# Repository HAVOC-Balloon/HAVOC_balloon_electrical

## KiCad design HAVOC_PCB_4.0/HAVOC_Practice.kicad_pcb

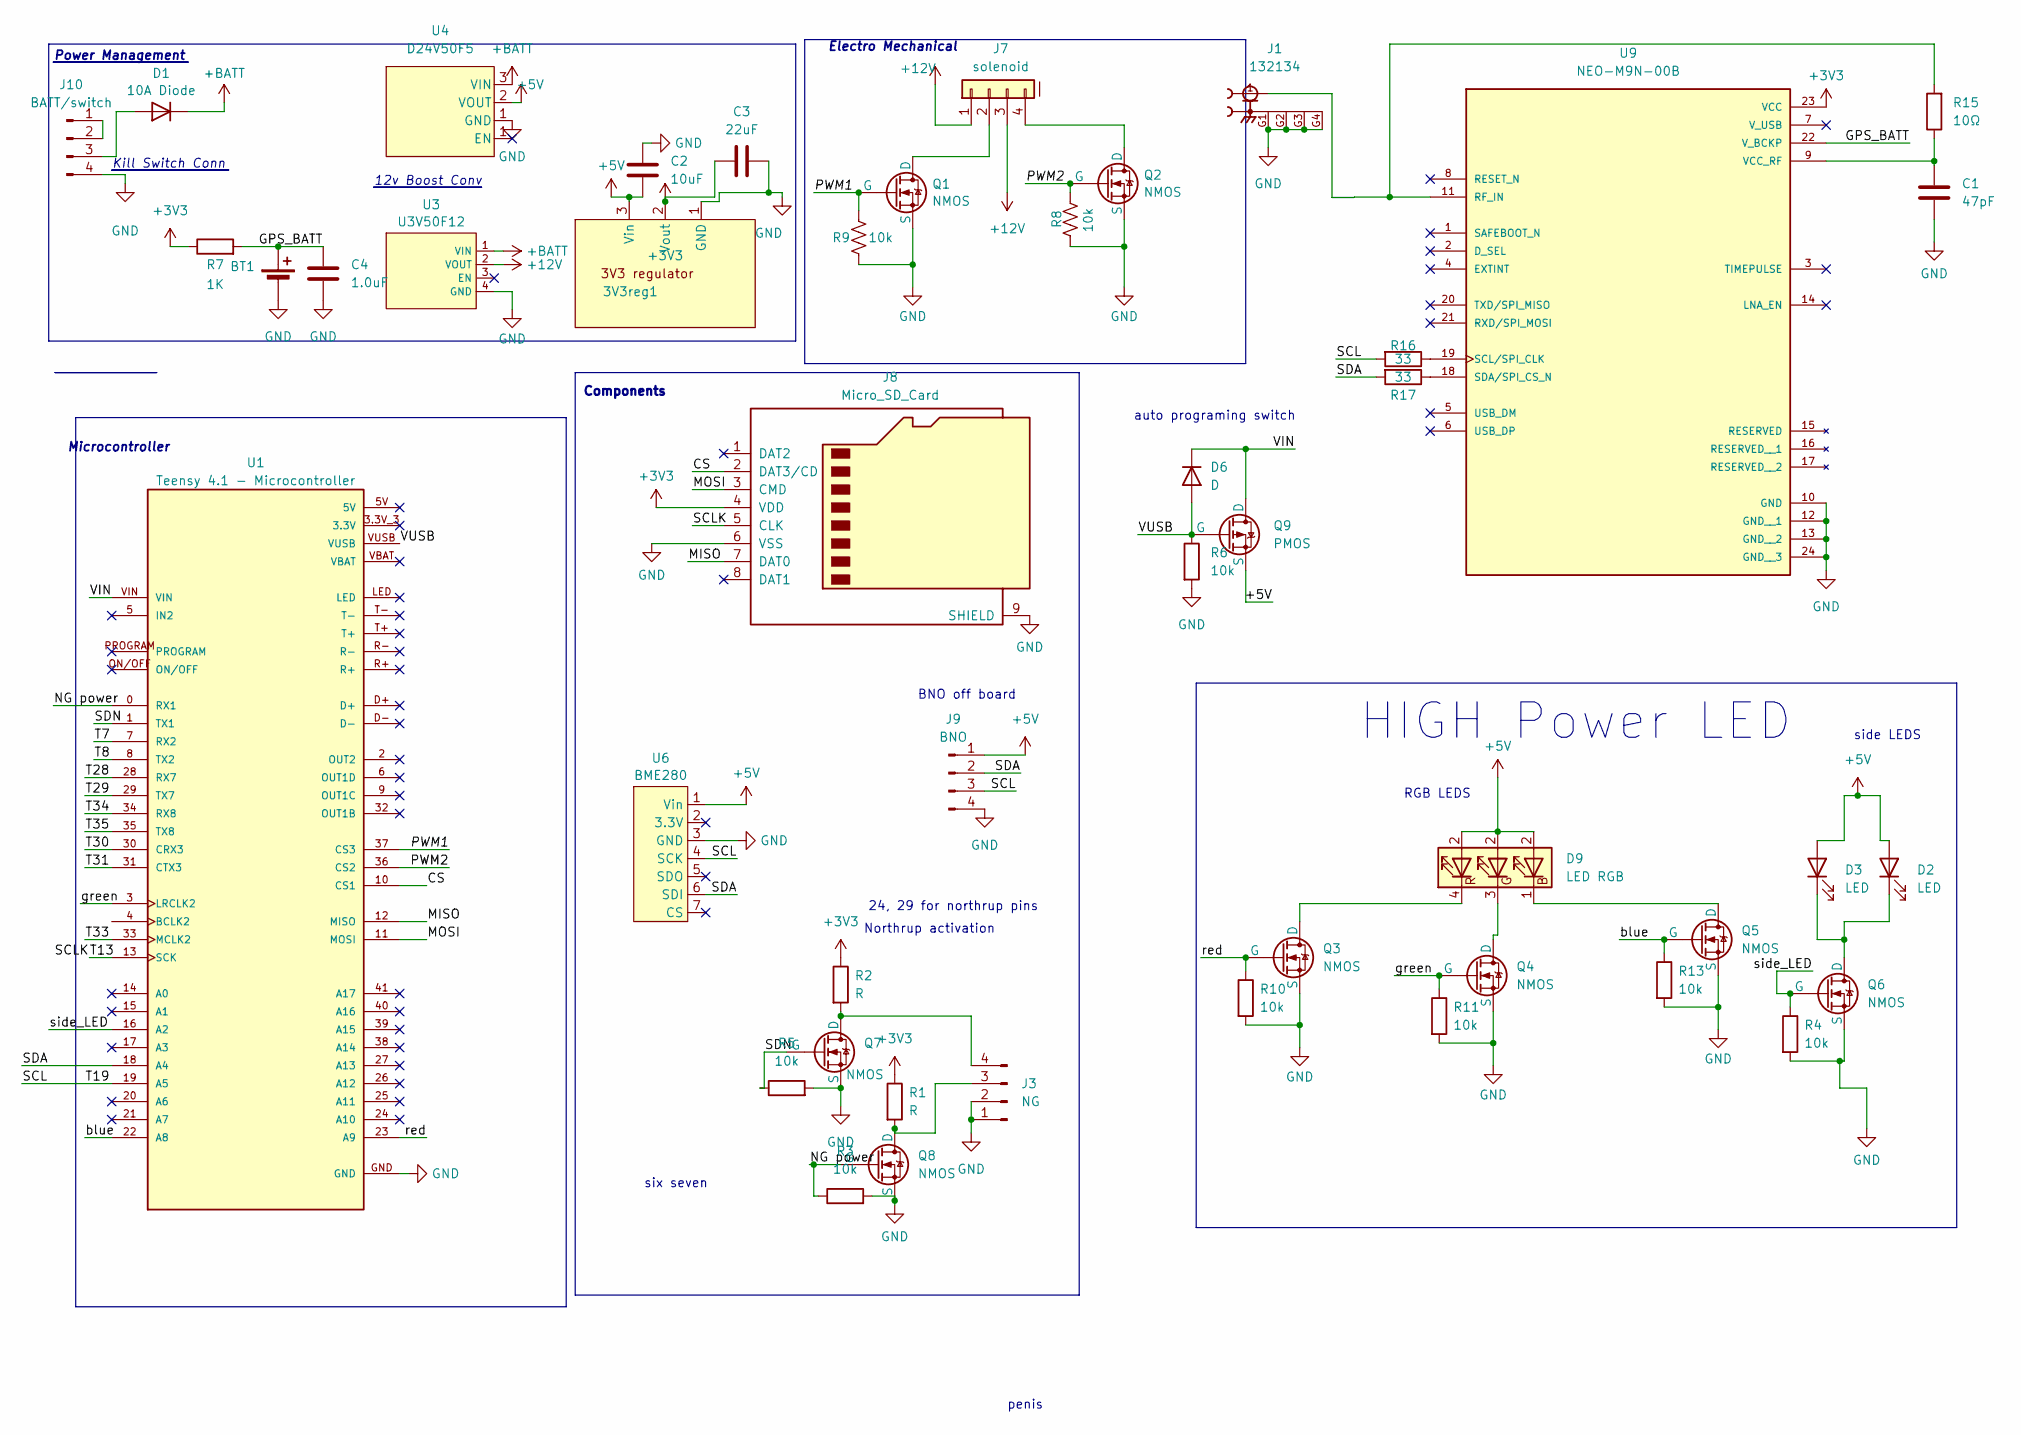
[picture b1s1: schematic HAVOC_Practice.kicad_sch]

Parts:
3V3reg1: SOT223-5_DIO-M
BT1: Battery_Cell; GPS_BATT
C1: 47pF; C_0603_1608Metric_Pad1.08x0.95mm_HandSolder
C2: 10uF; C_0603_1608Metric_Pad1.08x0.95mm_HandSolder
C3: 22uF; C_0603_1608Metric_Pad1.08x0.95mm_HandSolder
C4: 1.0uF; C_0603_1608Metric_Pad1.08x0.95mm_HandSolder
D1: 10A Diode; HAVOC diode
D2, D3: LED; Molex_Mini-Fit_Jr_5569-02A2_2x01_P4.20mm_Horizontal
D6: D; HAVOC diode
D9: LED RGB; Molex_Mini-Fit_Jr_5569-04A2_2x02_P4.20mm_Horizontal
J1: 132134; AMPHENOL_132134_SMA; PARTREV E
J3: NG; Molex_Mini-Fit_Jr_5569-04A2_2x02_P4.20mm_Horizontal
J7: solenoid; Molex_Mini-Fit_Jr_5569-04A2_2x02_P4.20mm_Horizontal
J8: Micro_SD_Card; SPI_SD
J9: BNO; Molex_Mini-Fit_Jr_5569-04A2_2x02_P4.20mm_Horizontal
J10: BATT/switch; Molex_Mini-Fit_Jr_5569-04A2_2x02_P4.20mm_Horizontal
Q1, Q2, Q3, Q4, Q5, Q6, Q7, Q8: NMOS; SOT23_DMG3406_DIO
Q9: PMOS; TO-220AB_LTO
R1, R2: R; R_0603_1608Metric_Pad0.98x0.95mm_HandSolder
R3, R4, R5, R6, R8, R9, R10, R11, R13: 10k; R_0603_1608Metric_Pad0.98x0.95mm_HandSolder
R7: 1K; R_0603_1608Metric_Pad0.98x0.95mm_HandSolder
R15: 10Ω; R_0603_1608Metric_Pad0.98x0.95mm_HandSolder
R16, R17: 33; R_0603_1608Metric_Pad0.98x0.95mm_HandSolder
U1: Teensy 4.1 - Microcontroller; MODULE_Teensy4-1-H4.0; PARTREV 4.1
U3: U3V50F12; U3V50F12_12V_REG
U4: D24V50F5; Pololu 5v Reg
U6: BME280
U9: NEO-M9N-00B; XCVR_NEO-M9N-00B; PARTREV R05

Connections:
+3V3: 3V3reg1.2 (Vout), C3.2, J8.4 (VDD), R1.1, R2.1, R7.1, U9.23 (VCC)
+5V: 3V3reg1.3 (Vin), C2.2, D2.1 (A), D3.1 (A), D9.2 (R), J9.1, Q9.3 (S), U4.2 (VOUT), U6.1 (Vin)
+12V: J7.1, J7.3, U3.2 (VOUT)
+BATT: D1.1 (K), U3.1 (VIN), U4.3 (VIN)
/CS: J8.2 (DAT3/CD), U1.10 (CS1)
/GPS_BATT: BT1.1 (+), C4.1, R7.2, U9.22 (V_BCKP)
/MISO: J8.7 (DAT0), U1.12 (MISO)
/MOSI: J8.3 (CMD), U1.11 (MOSI)
/NG power: Q8.2 (G), R3.1, U1.0 (RX1)
/PWM1: Q1.2 (G), R9.1, U1.37 (CS3)
/PWM2: Q2.2 (G), R8.1, U1.36 (CS2)
/SCL: J9.3, R16.2, U1.19 (A5), U6.4 (SCK)
/SCLK: J8.5 (CLK), U1.13 (SCK)
/SDA: J9.2, R17.2, U1.18 (A4), U6.6 (SDI)
/SDN: Q7.2 (G), R5.1, U1.1 (TX1)
/T7: U1.7 (RX2)
/T8: U1.8 (TX2)
/T28: U1.28 (RX7)
/T29: U1.29 (TX7)
/T30: U1.30 (CRX3)
/T31: U1.31 (CTX3)
/T33: U1.33 (MCLK2)
/T34: U1.34 (RX8)
/T35: U1.35 (TX8)
/VIN: D6.1 (K), Q9.1 (D), U1.VIN
/VUSB: D6.2 (A), Q9.2 (G), R6.1, U1.VUSB
/blue: Q5.2 (G), R13.1, U1.22 (A8)
/green: Q4.2 (G), R11.1, U1.3 (LRCLK2)
/red: Q3.2 (G), R10.1, U1.23 (A9)
/side_LED: Q6.2 (G), R4.1, U1.16 (A2)
GND: 3V3reg1.1 (GND), BT1.2 (-), C1.2, C2.1, C3.1, C4.2, J1.G1, J1.G2, J1.G3, J1.G4, J3.1, J3.2, J8.6 (VSS), J8.9 (SHIELD), J9.4, J10.4, Q1.3 (S), Q2.3 (S), Q3.3 (S), Q4.3 (S), Q5.3 (S), Q6.3 (S), Q7.3 (S), Q8.3 (S), R3.2, R4.2, R5.2, R6.2, R8.2, R9.2, R10.2, R11.2, R13.2, U1.GND, U3.4 (GND), U4.1 (GND), U6.3 (GND), U9.10 (GND), U9.12 (GND__1), U9.13 (GND__2), U9.24 (GND__3)
unnamed: D1.2 (A), J10.3
unnamed: D2.2 (K), D3.2 (K), Q6.1 (D)
unnamed: D9.1 (BK), Q5.1 (D)
unnamed: D9.3 (GK), Q4.1 (D)
unnamed: D9.4 (RK), Q3.1 (D)
unnamed: J3.3, Q8.1 (D), R1.2
unnamed: J3.4, Q7.1 (D), R2.2
unnamed: J7.2, Q1.1 (D)
unnamed: J10.1, J10.2
unnamed: J7.4, Q2.1 (D)
unnamed: J1.1, R15.2, U9.11 (RF_IN)
unnamed: R16.1, U9.19 (SCL/SPI_CLK)
unnamed: R17.1, U9.18 (SDA/SPI_CS_N)
unnamed: C1.1, R15.1, U9.9 (VCC_RF)

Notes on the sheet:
BNO off board
auto programing switch
12v Boost Conv
24, 29 for northrup pins
Components
Electro Mechanical
Kill Switch Conn
Microcontroller
Northrup activation
penis
six seven
HIGH Power LED
Power Management
RGB LEDS
side LEDS

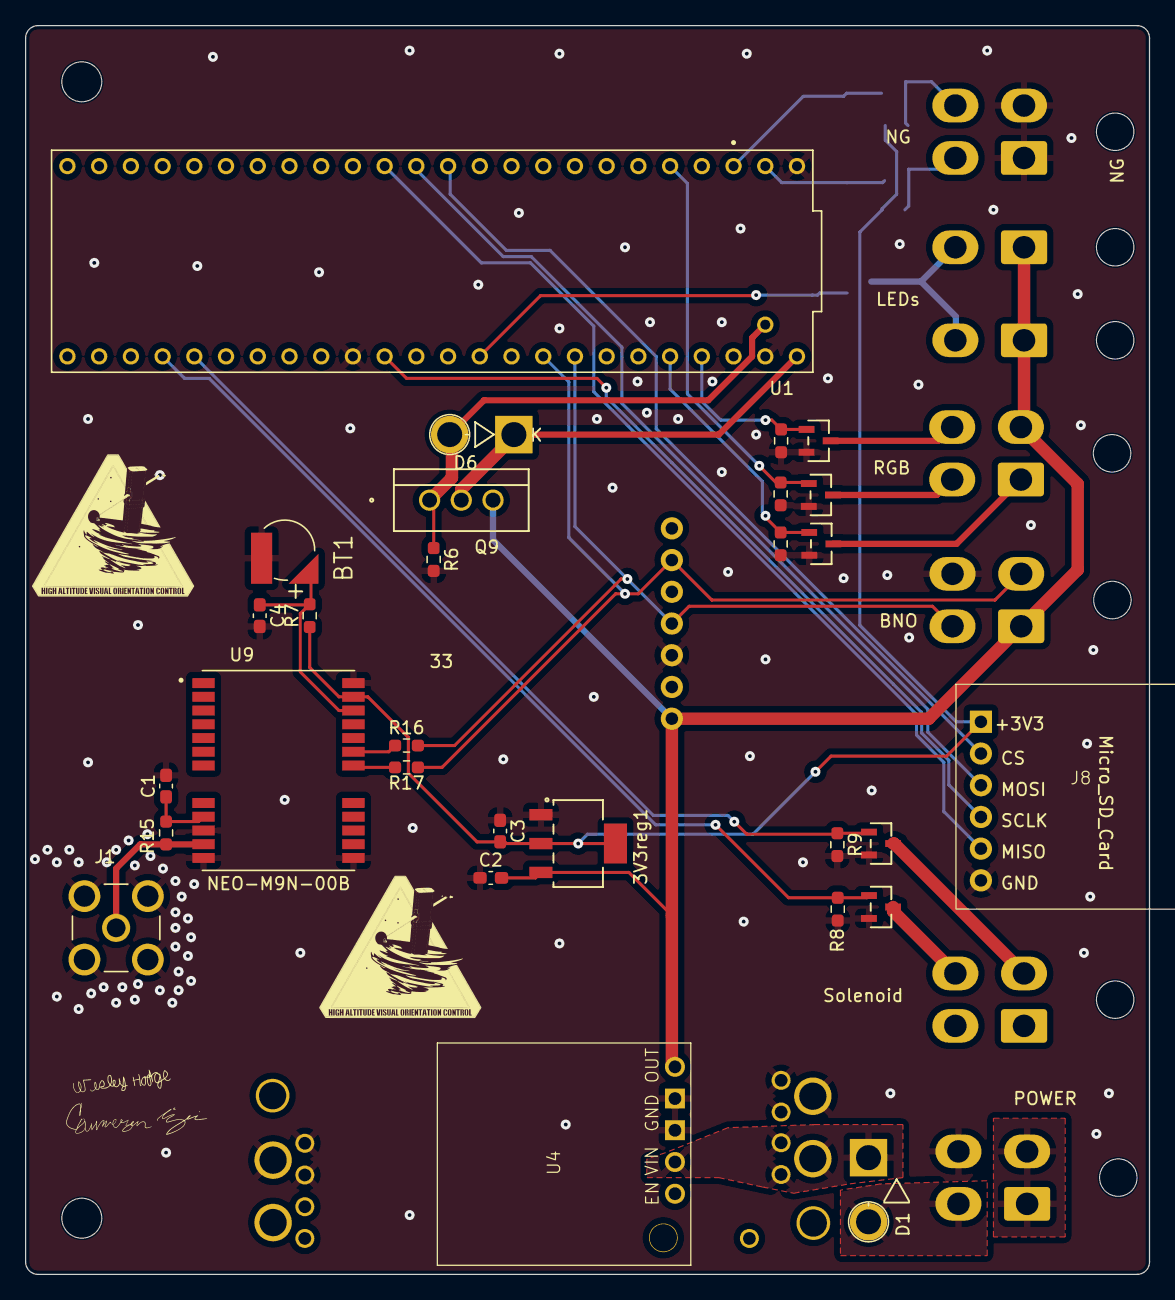
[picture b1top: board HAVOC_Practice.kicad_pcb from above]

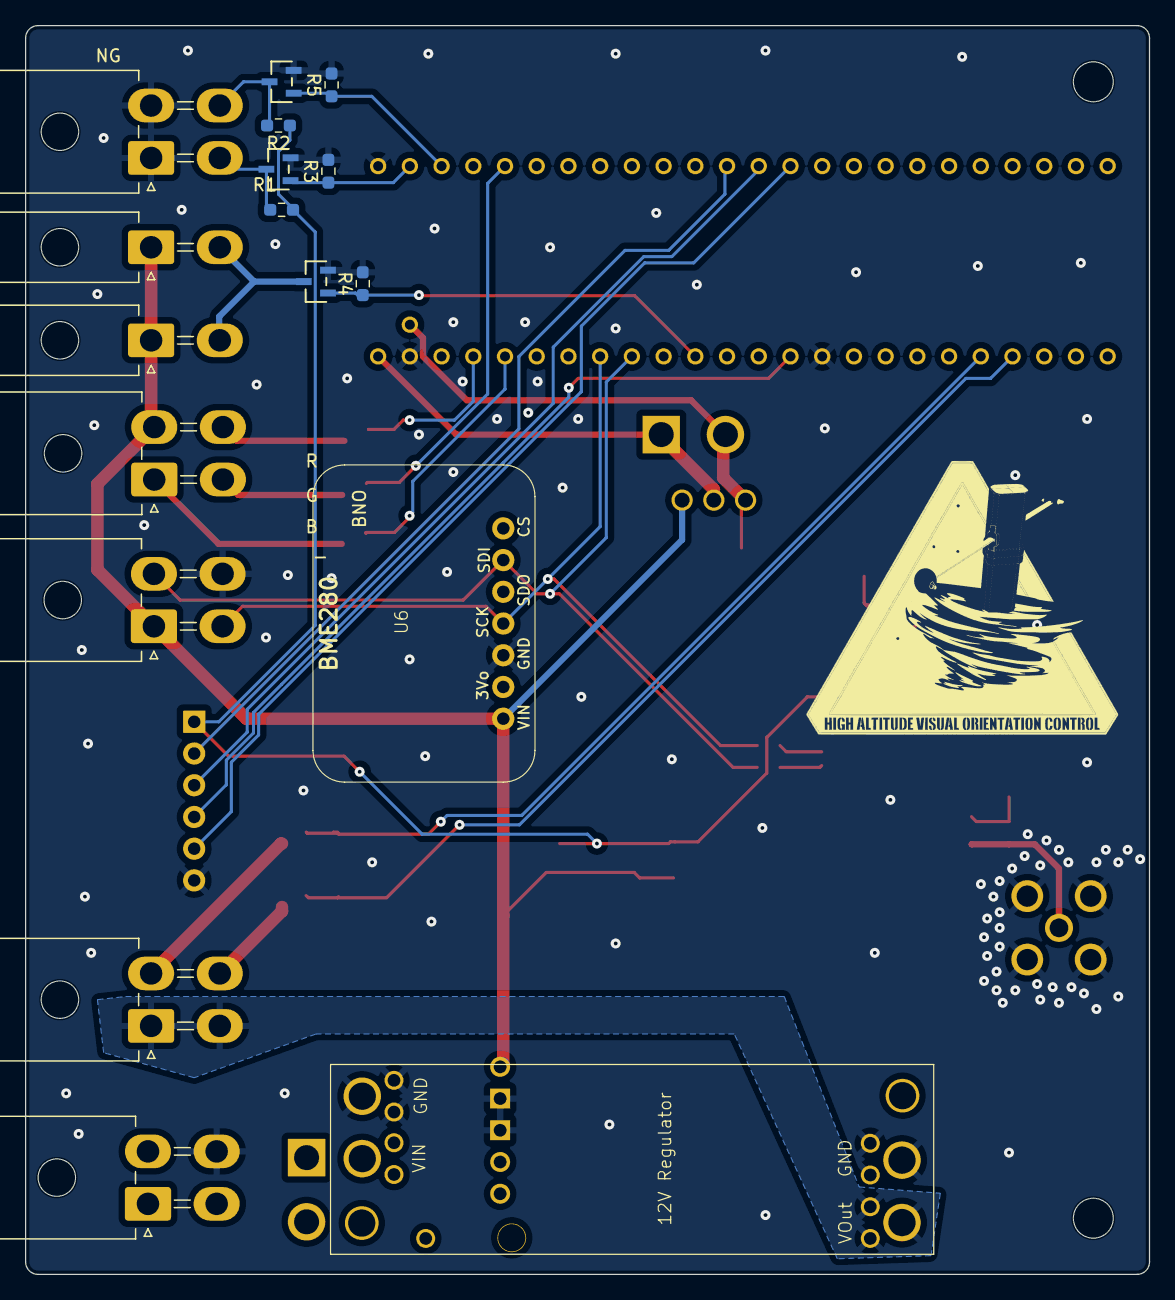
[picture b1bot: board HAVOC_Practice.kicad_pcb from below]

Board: 2 copper layers, 90.0 x 100.0 mm, 46 parts (17 on the bottom side), 36 nets.

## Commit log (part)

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2026-01-24 ahhh
2026-01-24 test branch
2026-01-24 test con
2026-01-24 wiring new connectors
2026-01-27 adding traces, still needs solenoid traces mich have to change pins
2026-01-30 penis
2026-01-30 hehehehehe
2026-01-31 six seven
2026-02-01 added backup battery and fixed missing PWM lines
2026-02-01 adding library items
2026-02-06 made mosfets for solenoids aligned so cam won't be displeased
2026-03-10 added 3d models
2026-03-10 adding 3d model files so they work on other computers
2026-05-20 adding 3D models
